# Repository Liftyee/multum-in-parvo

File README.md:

# multum-in-parvo
Low power, high performance mesh radio device

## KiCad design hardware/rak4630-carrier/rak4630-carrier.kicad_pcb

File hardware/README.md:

# Multum in Parvo — KiCad 8 engineering draft

**Revision A is still under development. Do not order or populate this draft.** The native project uses KiCad 8 schematic format 20231120 and PCB format 20240108. Validation runs with installed `kicad-cli 8.0.9`; no KiCad 9/10 format conversion is used. Open `mesh-node.kicad_pro`. All symbols and footprints are project-local.

The schematic has been captured and passes ERC. PCB routing and ground-return review are in progress. The current DRC report records the outstanding connections; a report with zero clearance violations alone does not mean the board is complete. Fabrication release requires zero unconnected items, a deliberate RF/power layout review, and completion of the checks below.

## Architecture

Solar feeds AEM10300; its storage pin joins PACK+. The battery supplies transmit pulses directly. BQ29700 and two common-drain AO3400A N-channel MOSFETs interrupt the negative cell lead. **CELL_N belongs only to the cell connector and protection circuit. Every load, charger return, programmer ground and shield connects to system GND / PACK−.** Raw BAT+ and protected PACK+ are electrically the same positive conductor in this low-side protection topology.

TPS63900 makes always-on 3.3 V. STM32WLE5CCU6 uses its low-power RF output, pin 22, with the ST MB1720 high-band low-power matching circuit. Pin 23, the high-power output, remains unconnected. A BGS12SN6 selects TX/RX for the normal population. The alternate path uses SKY66423-11 with its EK3 868 MHz matching/filter network and pack-referenced controls. MAX17048 is optional. TPS22919 supplies a peripheral connector carrying switched power and GND only.

The system needs an STM32WLE5 firmware/board port; this hardware is not a claim of existing drop-in Meshtastic firmware compatibility.

## Stack and RF geometry

Proposed stack: 2 layers, 0.8 mm finished board, 35 µm copper per side, approximately 0.73 mm dielectric, FR-4 Er 4.5, ENIG, 20 µm soldermask with assumed Er 3.8. RF corridors use top grounded coplanar waveguide, 0.75 mm trace and 0.25 mm side gap, with a continuous bottom reference. The 2-D quasi-static finite-volume calculation gives **50.65 Ω** at 10 µm grid resolution and 50.46 Ω at 20 µm. See `reports/field-impedance.json`; the earlier conformal approximation is retained separately for comparison.

These are proposed material properties, not guaranteed JLCPCB controlled impedance. Confirm the actual offered 0.8 mm stack and measure a coupon. The finite-box calculation does not include pad launches, component parasitics, connector transitions or RF matching. Short narrow launches at fine-pitch parts require VNA tuning. Two layers are quantitatively feasible; a switch to four layers is not justified by the line width.

Ordinary clearance is 0.15 mm, with 0.20 mm ordinary signal routing preferred where space allows. Vias use 0.60/0.30 mm copper/drill. Power routing uses wider conductors and will be reviewed for bottlenecks before release. RF signal routing is restricted to the top layer. Routing output alone is not sufficient: copper pours, stitching and visual ground continuity must also pass review.

## Configuration and operating assumptions

- Solar panel **worst-case cold Voc ≤4.3 V**, providing margin below AEM10300's 4.5 V recommended SRC limit. Its 5.5 V absolute maximum is not an operating target. A nominal 6 V panel is unsuitable.
- AEM10300 straps: STO_CFG=0000 gives 4.05 V charge, 3.50 V ready and 3.00 V low status; R_MPP=100 selects 80% Voc; T_MPP=01 selects nominal 4.5 s/70.8 ms sampling. EN_HP is high; charge is independently inhibited by the temperature/solar-valid logic and MCU.
- Four 100 µF/10 V/1210 storage capacitors are provided. The manufacturer requires at least 100 µF **effective** capacitance with an absent battery. DC-bias/temperature derating of the exact selected capacitor remains a release check.
- TPS63900: CFG3=16.2 kΩ for 3.3 V at SEL=0; CFG1=36.5 kΩ and CFG2=0 also select 3.3 V/unlimited current in the alternate state. Configuration resistors are 1%.
- BQ29700 nominal overcharge/undervoltage levels are 4.275/2.800 V. Normal firmware operating floor is 3.0 V with burst-droop margin. Protection is independent of firmware.
- AO3400A replaces CSD16301Q2 because it specifies ≤48 mΩ at 2.5 V gate drive. Two devices give ≤96 mΩ at 25 °C: 28.8 mV drop and 8.64 mW at 300 mA, excluding traces/connectors. Temperature and protection-threshold tolerances still need inclusion in the final current-path review.
- AQ3118E-01ETG replaces the suggested ESD part: 18 V bidirectional standoff and 0.3 pF typical capacitance accommodate the 7.08 V RF peak at +27 dBm into 50 Ω. A 5 V standoff diode is inappropriate at that power. ESD system performance must be tested.

## RF firmware requirements

BGS12SN6 draws 100 µA typical/180 µA maximum while powered. PA11 supplies its VDD, following the GPIO-supply option in the ST reference. Before sleep set CTRL=0, then PA11=0; keep CTRL low while the switch is unpowered. On wake drive PA11 high and wait at least 20 µs before transmitting. CTRL=0 selects RF1/TX; CTRL=1 selects RF2/RX.

FEM controls have pack-referenced high levels and default low. Allow at least 1 ms for the high-value level-translation networks to settle. Configure the radio's LP PA, start at −9 dBm conducted drive, verify output with an attenuator/load and spectrum analyzer, and never exceed the FEM's +10 dBm TX-input absolute maximum. Firmware must enforce regional output-power, antenna-gain and duty-cycle restrictions. +27 dBm is not universally permitted in EU868.

## Estimated standby budget

No board current has been measured. Typical component figures are not worst-case system guarantees.

| Contributor | Approximate standby contribution | Conditions |
|---|---:|---|
| BQ29700 | 4 µA | Omitted with externally protected pack |
| TPS63900 | 0.075 µA | Typical quiescent figure, conversion losses additional |
| STM32WLE5 | ~1 µA class | Stop 2 + RTC; configuration dependent |
| TPS22919 | 0.002 µA typical | OFF; datasheet permits up to 0.8 µA over full temperature |
| MAX17048 | ~3 µA | Hibernate, optional/DNP; active mode higher |
| BGS12SN6 | Supply driven low in sleep | GPIO/switch leakage must be measured |
| Temperature divider | No direct battery divider load | Powered from solar-valid output only |
| Temperature comparators/supervisor | Solar supplied | ~0.82 µA nominal combined IC current |
| AEM10300 | Unresolved in selected high-power mode | 5.9 nA figure applies to EN_HP=LOW, not the selected HIGH strap |
| FEM and translation | Optional/DNP | Shutdown leakage needs full-temperature audit |

Known default contributions are about 5.1 µA before AEM high-power-mode current, GPIO/MOSFET leakage, capacitor leakage and converter losses. The single-digit ancillary target is plausible but **not yet verified**. A continuously high BGS supply would alone defeat it; the circuit now explicitly avoids that.

## Bring-up sequence after layout release

1. Inspect all bridges, orientation marks, exposed pads and mutually exclusive population options. Leave antenna disconnected and all supplies off.
2. Check resistance between PACK+, GND and CELL_N. Verify protection MOSFET body-diode orientation. Use a current-limited battery simulator before attaching a cell.
3. Verify BQ cutoff/recovery and confirm that solar, debug and peripheral grounds cannot bypass the protector.
4. Sweep the temperature sensor resistance and solar voltage. Confirm EN_STO_CH goes low for absent/shorted NTC, out-of-window temperature, reset MCU and insufficient solar voltage. Measure response delay and leakage.
5. Check 3V3_AON, regulator startup, ripple and droop with pulsed loads. Verify all RF supply nodes before enabling the radio.
6. Attach SWD, test both oscillators, calibrate HSE loading/trim, verify RTC and deep-sleep current with debug detached.
7. Test normal RF with a suitable conducted load/attenuation. Tune matching and filter values with a VNA; measure harmonics, RX sensitivity and switching transients.
8. Fit the FEM variant only after the normal radio works. Verify control truth table/default shutdown and output power starting at minimum drive. Repeat spectral, RX and current-pulse checks.
9. Repeat temperature, battery cutoff/recovery, absent-battery and low-light tests across the intended operating range. Attach the real battery last.

## Release checks still open

Finish routing and ground pours/stitching; inspect both layers; resolve DRC including connectivity and schematic parity; verify every custom footprint against the manufacturer's drawing; verify exact capacitor derating and inductor land patterns; close charge-enable pullup/logic margins and temperature qualification; audit crystal startup/load/frequency tolerance; audit all sleep leakage at temperature; finish silk/test-point labels and connector orientation review. Only then export a fabrication set, assembly positions and final BOM.

See `population-options.md`, `temperature-analysis.md`, `sources/urls.json` and `reports/` for supporting material. Draft BOM entries that contain only an electrical value still require a purchasable manufacturer part number before fabrication release.

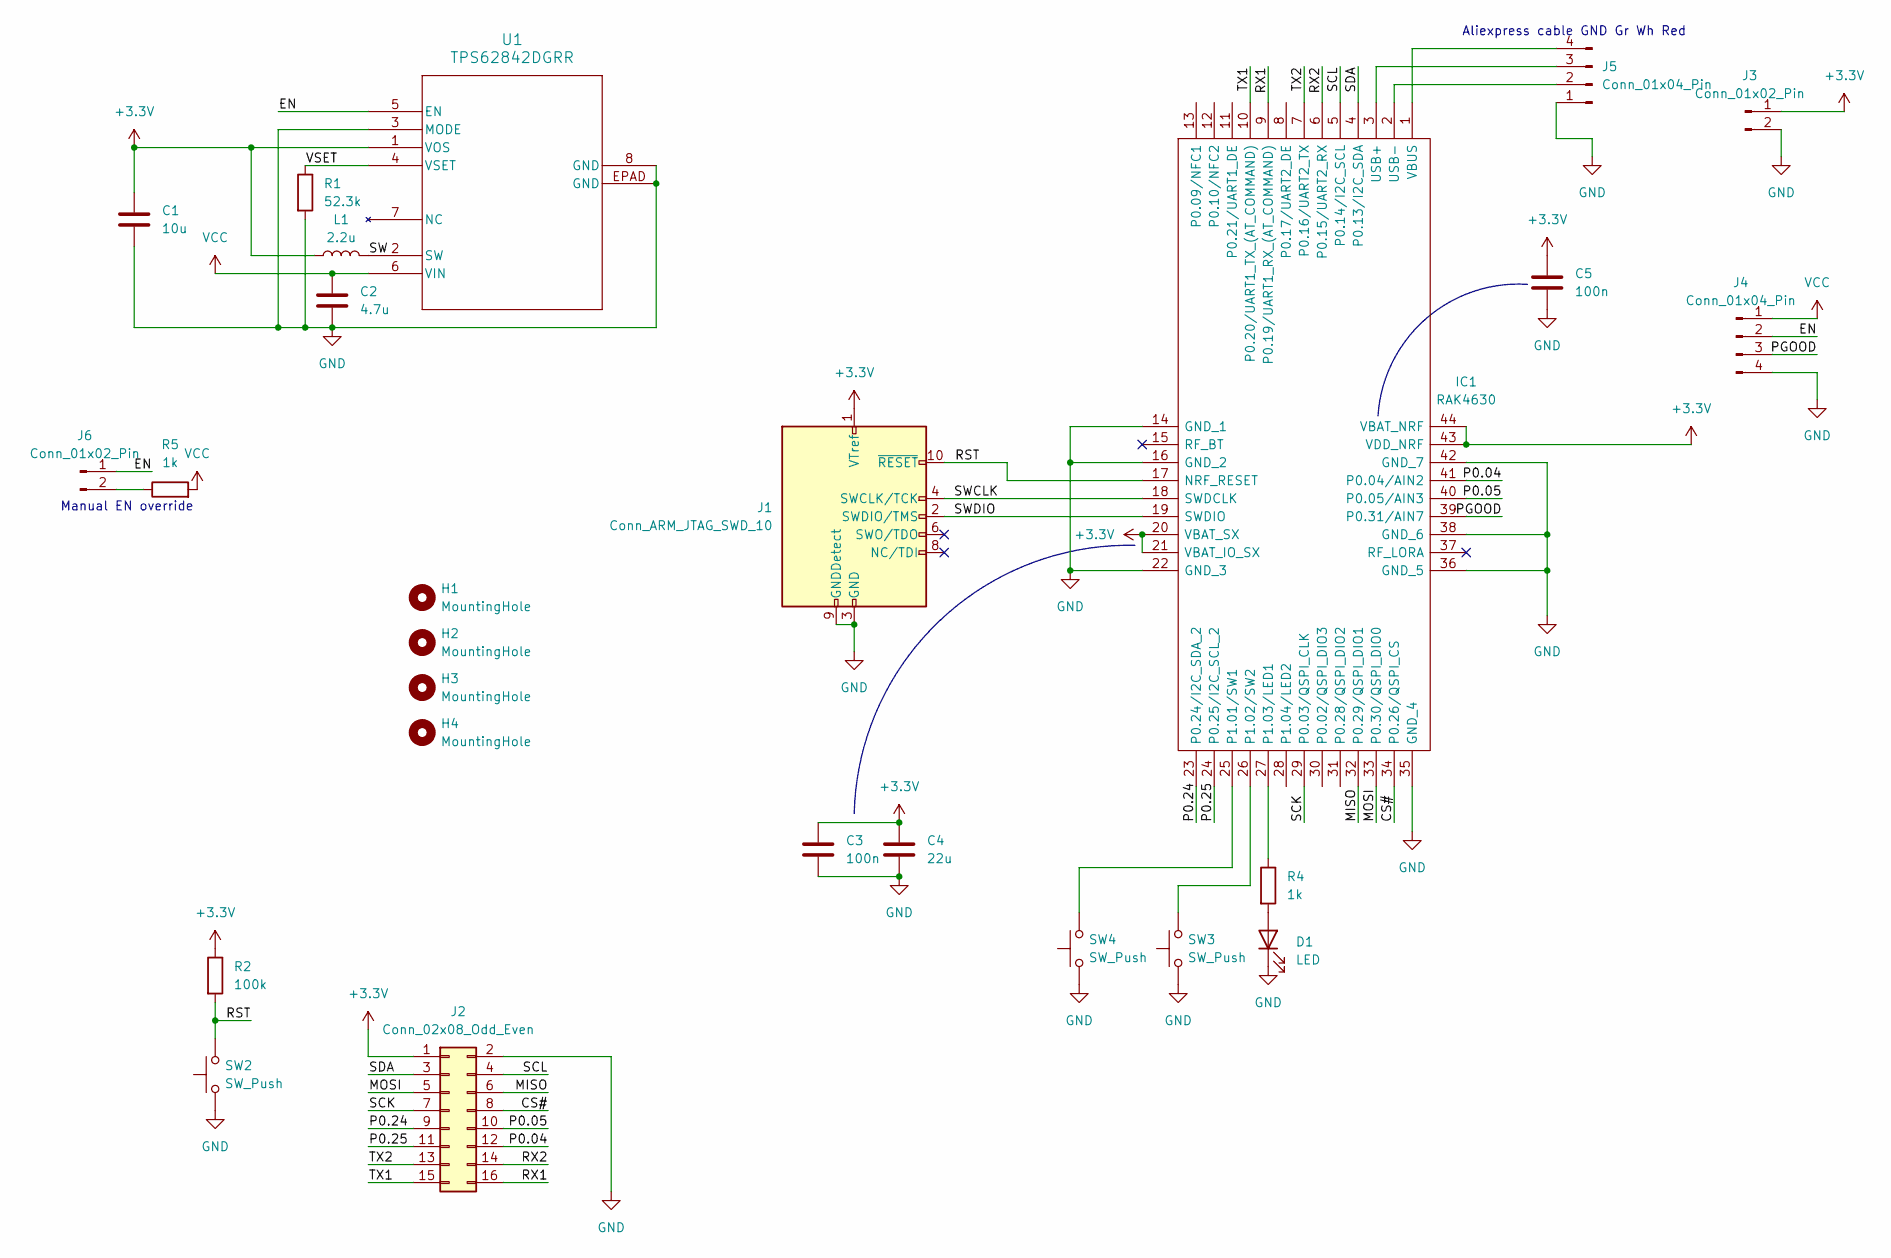
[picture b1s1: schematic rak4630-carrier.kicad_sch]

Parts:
C1: 10u; C_0805_2012Metric
C2: 4.7u; C_0805_2012Metric
C3, C5: 100n; C_0805_2012Metric
C4: 22u; C_0805_2012Metric
D1: LED; LED_0805_2012Metric
H1, H2, H3, H4: MountingHole; MountingHole_3.2mm_M3
IC1: RAK4630; Manufacturer_Part_Number RAK4630
J1: Conn_ARM_JTAG_SWD_10; PinHeader_2x05_P1.27mm_Vertical
J2: Conn_02x08_Odd_Even; PinHeader_2x08_P2.54mm_Vertical
J3: Conn_01x02_Pin; JST_XH_B2B-XH-A_1x02_P2.50mm_Vertical
J4: Conn_01x04_Pin; JST_XH_B4B-XH-A_1x04_P2.50mm_Vertical
J5: Conn_01x04_Pin; JST_PH_B4B-PH-K_1x04_P2.00mm_Vertical
J6: Conn_01x02_Pin; PinHeader_1x02_P2.54mm_Vertical
L1: 2.2u; L_Murata_DFE201610P
R1: 52.3k; R_0805_2012Metric
R2: 100k; R_0805_2012Metric
R4, R5: 1k; R_0805_2012Metric
SW2, SW3, SW4: SW_Push; Aliexpress_TLZWLA_SMD_Button_4mm
U1: TPS62842DGRR; HVSSOP8_DGR_TEX

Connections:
+3.3V: C1.1, C3.1, C4.1, C5.1, IC1.20 (VBAT_SX), IC1.21 (VBAT_IO_SX), IC1.43 (VDD_NRF), IC1.44 (VBAT_NRF), J1.1 (VTref), J2.1, J3.1, L1.1, R2.1, U1.1 (VOS)
/CS#: IC1.34 (P0.26/QSPI_CS), J2.8
/EN: J4.2, J6.1, U1.5 (EN)
/MISO: IC1.32 (P0.29/QSPI_DIO1), J2.6
/MOSI: IC1.33 (P0.30/QSPI_DIO0), J2.5
/P0.04: IC1.41 (P0.04/AIN2), J2.12
/P0.05: IC1.40 (P0.05/AIN3), J2.10
/P0.24: IC1.23 (P0.24/I2C_SDA_2), J2.9
/P0.25: IC1.24 (P0.25/I2C_SCL_2), J2.11
/PGOOD: IC1.39 (P0.31/AIN7), J4.3
/RST: IC1.17 (NRF_RESET), J1.10 (~RESET), R2.2, SW2.2
/RX1: IC1.9 (P0.19/UART1_RX_(AT_COMMAND)), J2.16
/RX2: IC1.6 (P0.15/UART2_RX), J2.14
/SCK: IC1.29 (P0.03/QSPI_CLK), J2.7
/SCL: IC1.5 (P0.14/I2C_SCL), J2.4
/SDA: IC1.4 (P0.13/I2C_SDA), J2.3
/SW: L1.2, U1.2 (SW)
/SWCLK: IC1.18 (SWDCLK), J1.4 (SWCLK/TCK)
/SWDIO: IC1.19 (SWDIO), J1.2 (SWDIO/TMS)
/TX1: IC1.10 (P0.20/UART1_TX_(AT_COMMAND)), J2.15
/TX2: IC1.7 (P0.16/UART2_TX), J2.13
/VSET: R1.1, U1.4 (VSET)
GND: C1.2, C2.2, C3.2, C4.2, C5.2, D1.1 (K), IC1.14 (GND_1), IC1.16 (GND_2), IC1.22 (GND_3), IC1.35 (GND_4), IC1.36 (GND_5), IC1.38 (GND_6), IC1.42 (GND_7), J1.3 (GND), J1.5 (GND), J1.9 (GNDDetect), J2.2, J3.2, J4.4, J5.1, R1.2, SW2.1, SW3.1, SW4.1, U1.3 (MODE), U1.8 (GND), U1.EPAD (GND)
unnamed: D1.2 (A), R4.2
unnamed: IC1.25 (P1.01/SW1), SW4.2
unnamed: IC1.26 (P1.02/SW2), SW3.2
unnamed: IC1.27 (P1.03/LED1), R4.1
unnamed: IC1.3 (USB+), J5.3
unnamed: IC1.2 (USB-), J5.2
unnamed: IC1.1 (VBUS), J5.4
unnamed: J6.2, R5.1
VCC: C2.1, J4.1, R5.2, U1.6 (VIN)

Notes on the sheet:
Manual EN override
Aliexpress cable GND Gr Wh Red

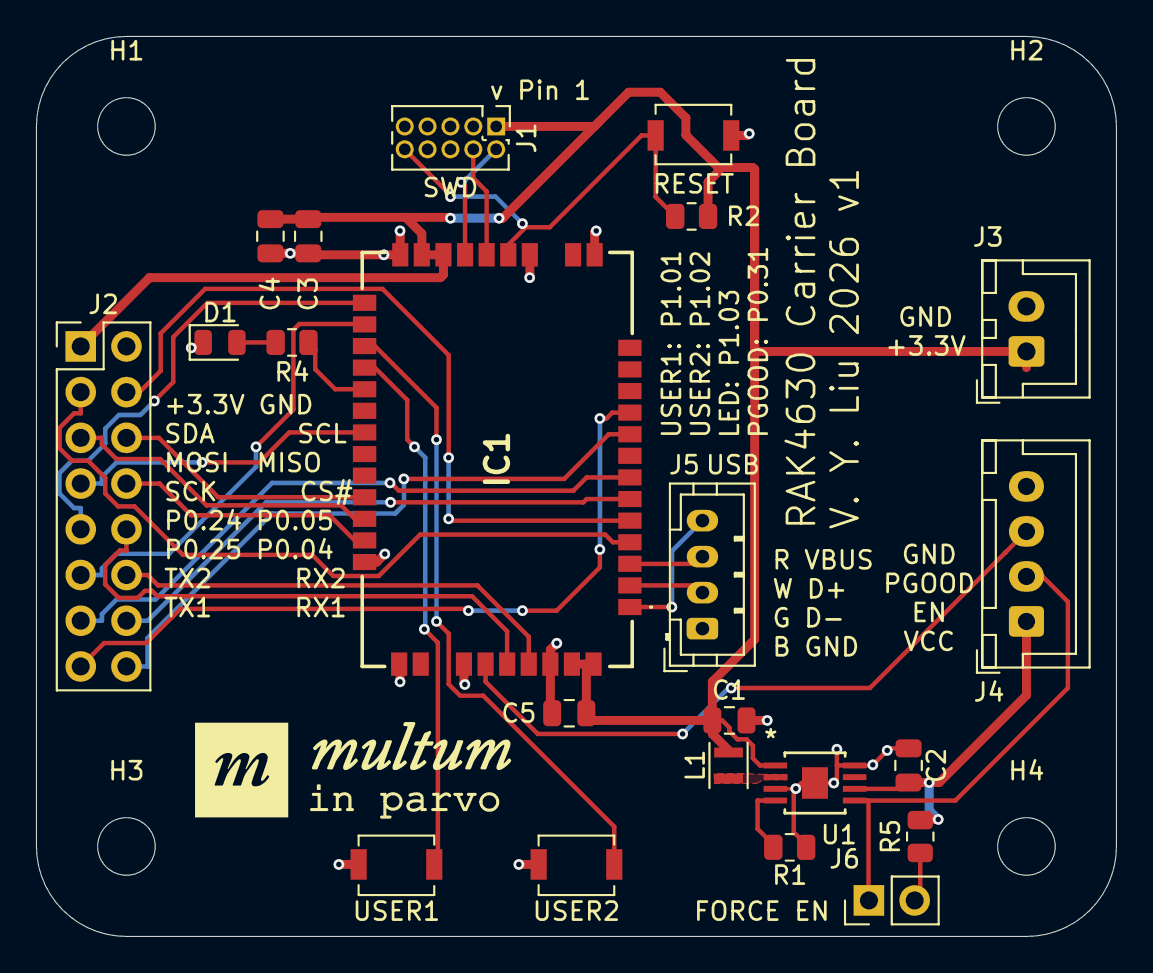
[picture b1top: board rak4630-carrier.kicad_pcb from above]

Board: 2 copper layers, 60.0 x 50.0 mm, 26 parts (0 on the bottom side), 32 nets.

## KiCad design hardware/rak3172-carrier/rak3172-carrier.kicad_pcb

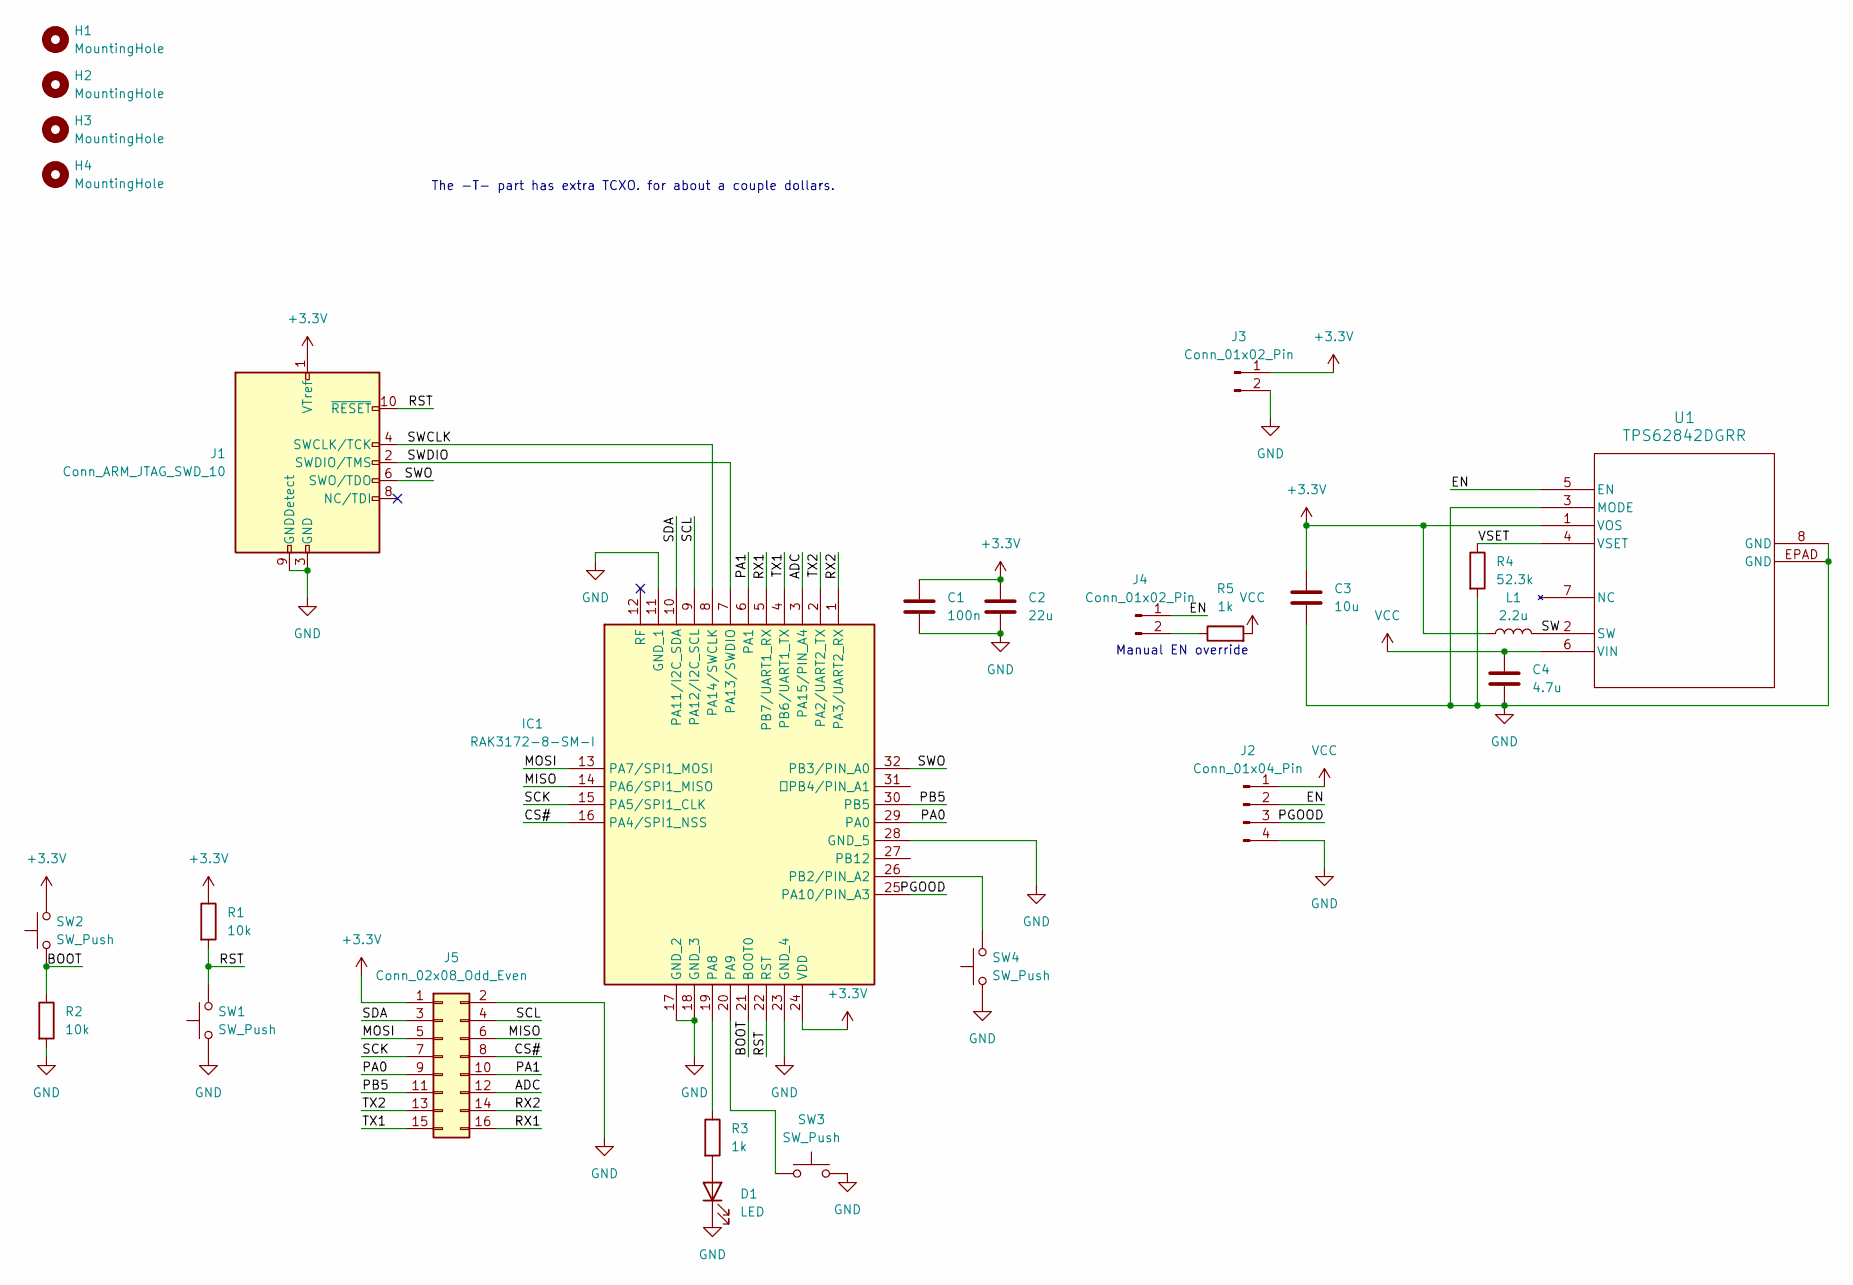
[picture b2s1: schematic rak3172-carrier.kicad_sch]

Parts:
C1: 100n; C_0805_2012Metric
C2: 22u; C_0805_2012Metric
C3: 10u; C_0805_2012Metric
C4: 4.7u; C_0805_2012Metric
D1: LED; LED_0805_2012Metric
H1, H2, H3, H4: MountingHole; MountingHole_3.2mm_M3
IC1: RAK3172-8-SM-I; RAK31729SMNI; Manufacturer_Part_Number RAK3172-9-SM-NI
J1: Conn_ARM_JTAG_SWD_10; PinHeader_2x05_P1.27mm_Vertical
J2: Conn_01x04_Pin; JST_XH_B4B-XH-A_1x04_P2.50mm_Vertical
J3: Conn_01x02_Pin; JST_XH_B2B-XH-A_1x02_P2.50mm_Vertical
J4: Conn_01x02_Pin; PinHeader_1x02_P2.54mm_Vertical
J5: Conn_02x08_Odd_Even; PinHeader_2x08_P2.54mm_Vertical
L1: 2.2u; L_Murata_DFE201610P
R1, R2: 10k; R_0805_2012Metric
R3, R5: 1k; R_0805_2012Metric
R4: 52.3k; R_0805_2012Metric
SW1, SW2, SW3, SW4: SW_Push; Aliexpress_TLZWLA_SMD_Button_4mm
U1: TPS62842DGRR; HVSSOP8_DGR_TEX

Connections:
+3.3V: C1.1, C2.1, C3.1, IC1.24 (VDD), J1.1 (VTref), J3.1, J5.1, L1.1, R1.1, SW2.2, U1.1 (VOS)
/ADC: IC1.3 (PA15/PIN_A4), J5.12
/BOOT: IC1.21 (BOOT0), R2.1, SW2.1
/CS#: IC1.16 (PA4/SPI1_NSS), J5.8
/EN: J2.2, J4.1, U1.5 (EN)
/MISO: IC1.14 (PA6/SPI1_MISO), J5.6
/MOSI: IC1.13 (PA7/SPI1_MOSI), J5.5
/PA0: IC1.29 (PA0), J5.9
/PA1: IC1.6 (PA1), J5.10
/PB5: IC1.30 (PB5), J5.11
/PGOOD: IC1.25 (PA10/PIN_A3), J2.3
/RST: IC1.22 (RST), J1.10 (~RESET), R1.2, SW1.2
/RX1: IC1.5 (PB7/UART1_RX), J5.16
/RX2: IC1.1 (PA3/UART2_RX), J5.14
/SCK: IC1.15 (PA5/SPI1_CLK), J5.7
/SCL: IC1.9 (PA12/I2C_SCL), J5.4
/SDA: IC1.10 (PA11/I2C_SDA), J5.3
/SW: L1.2, U1.2 (SW)
/SWCLK: IC1.8 (PA14/SWCLK), J1.4 (SWCLK/TCK)
/SWDIO: IC1.7 (PA13/SWDIO), J1.2 (SWDIO/TMS)
/SWO: IC1.32 (PB3/PIN_A0), J1.6 (SWO/TDO)
/TX1: IC1.4 (PB6/UART1_TX), J5.15
/TX2: IC1.2 (PA2/UART2_TX), J5.13
/VSET: R4.1, U1.4 (VSET)
GND: C1.2, C2.2, C3.2, C4.2, D1.1 (K), IC1.11 (GND_1), IC1.17 (GND_2), IC1.18 (GND_3), IC1.23 (GND_4), IC1.28 (GND_5), J1.3 (GND), J1.5 (GND), J1.9 (GNDDetect), J2.4, J3.2, J5.2, R2.2, R4.2, SW1.1, SW3.2, SW4.1, U1.3 (MODE), U1.8 (GND), U1.EPAD (GND)
unnamed: D1.2 (A), R3.2
unnamed: IC1.19 (PA8), R3.1
unnamed: IC1.20 (PA9), SW3.1
unnamed: IC1.26 (PB2/PIN_A2), SW4.2
unnamed: J4.2, R5.1
VCC: C4.1, J2.1, R5.2, U1.6 (VIN)

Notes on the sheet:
The -T- part has extra TCXO. for about a couple dollars.
Manual EN override

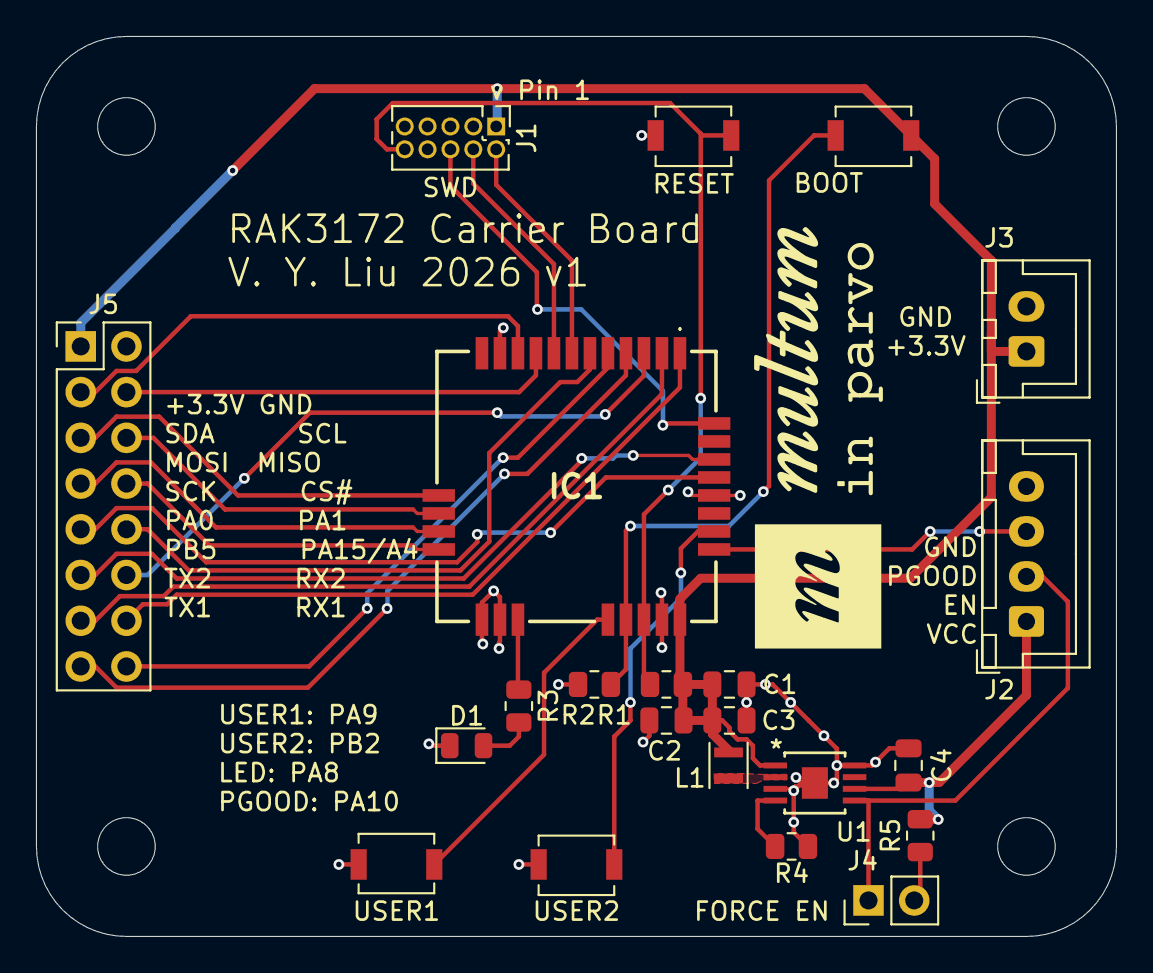
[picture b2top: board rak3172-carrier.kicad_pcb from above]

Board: 2 copper layers, 60.0 x 50.0 mm, 26 parts (0 on the bottom side), 31 nets.

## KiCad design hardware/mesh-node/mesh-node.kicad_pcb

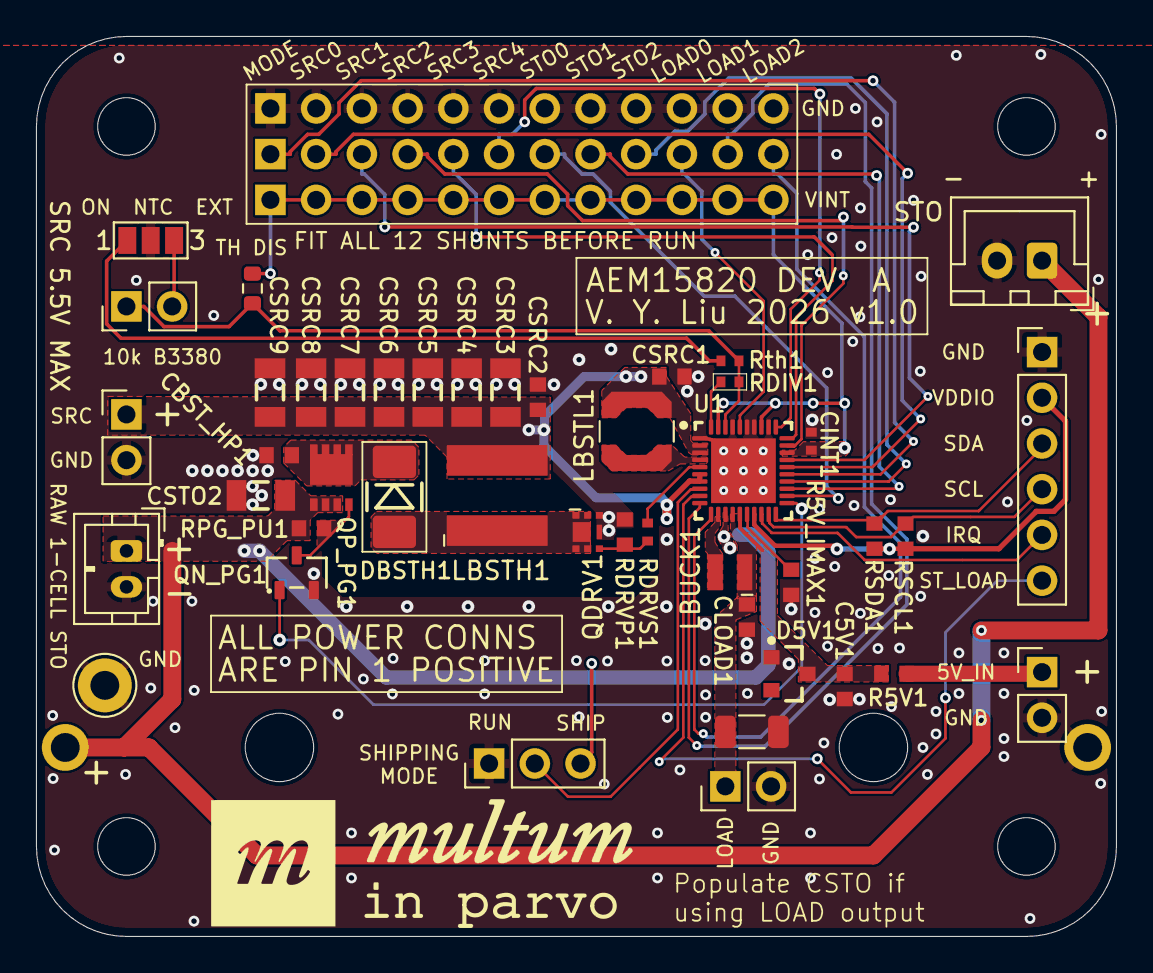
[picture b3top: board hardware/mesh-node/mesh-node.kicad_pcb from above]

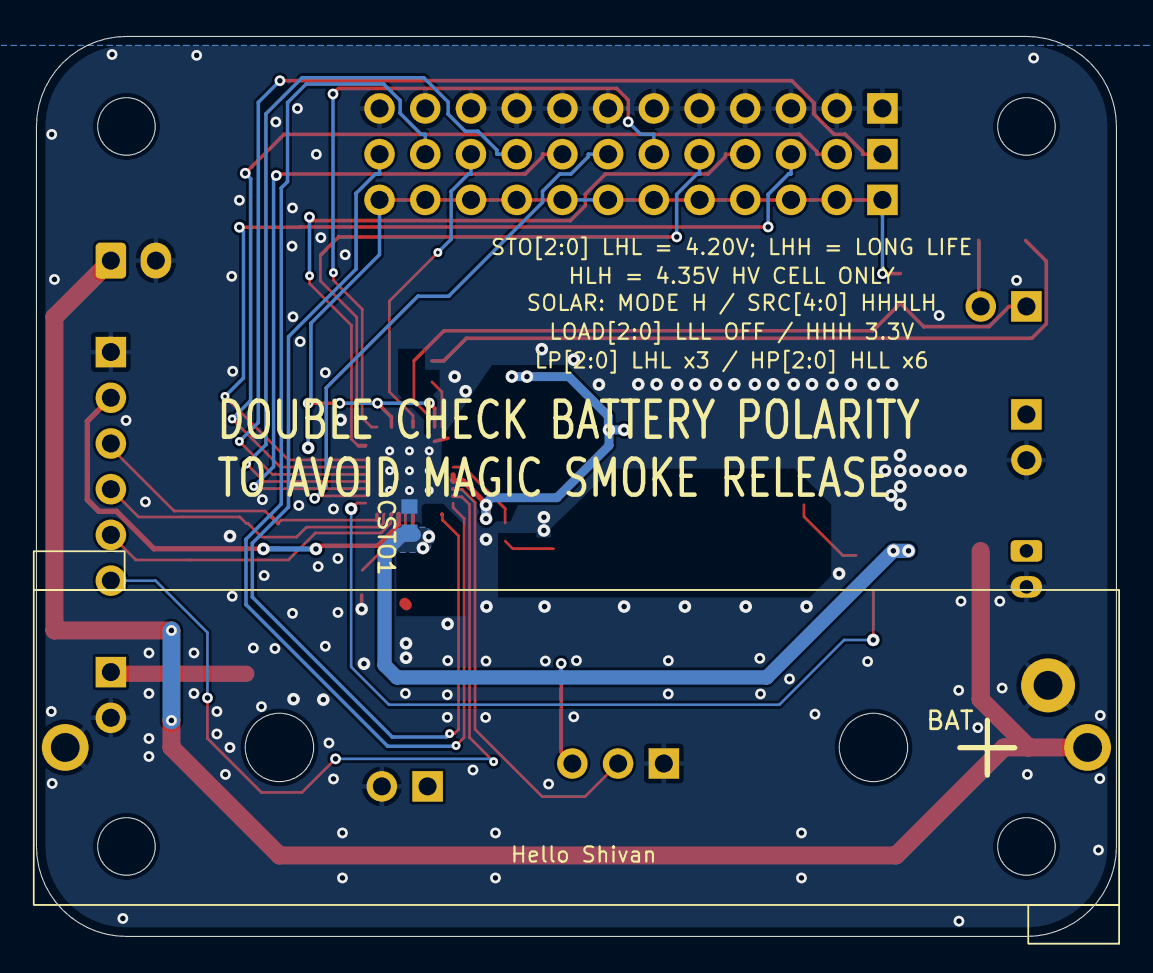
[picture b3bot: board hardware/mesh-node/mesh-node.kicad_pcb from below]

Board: 2 copper layers, 60.0 x 50.0 mm, 53 parts (2 on the bottom side), 38 nets.

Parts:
BAT: Bulgin BX0035 Battery Holder
C5V1: 47uF; AEM_Donor_C0603_[1608]
CBST_HP1: 47uF; AEM_Donor_C0603_[1608]
CINT1: 10uF; AEM_Donor_C0402_[1005]
CLOAD1: 22uF; AEM_Donor_C0603_[1608]
CLOAD2: OPTIONAL 220uF; C_1206_3216Metric
CSRC1, CSRC2: 22uF; AEM_Donor_C0603_[1608]
CSRC3, CSRC4, CSRC5, CSRC6, CSRC7, CSRC8, CSRC9: 220uF; AEM_Donor_C1206_[3216]
CSTO1: 47uF; AEM_Donor_C0603_[1608]
CSTO2: 220uF; AEM_Donor_C1206_[3216]
D5V1: 5.1V; AEM_Donor_SOT23-3P__3x1.40mm_Pitch=0.915mm_diode_AK
DBSTH1: VS-10BQ015; AEM_Donor_DO-214AA
H1, H2, H3, H4: M3; MountingHole_3.2mm_M3
J5V1: J5V1; PinHeader_1x02_P2.54mm_Vertical
JCFG1: LOW / GND; PinHeader_1x12_P2.54mm_Vertical
JCFG2: SIGNALS; PinHeader_1x12_P2.54mm_Vertical
JCFG3: HIGH / VINT; PinHeader_1x12_P2.54mm_Vertical
JIO1: JIO1; PinHeader_1x06_P2.54mm_Vertical
JLOAD1: JLOAD1; PinHeader_1x02_P2.54mm_Vertical
JNTC1: EXT NTC 10k B3380; PinHeader_1x02_P2.54mm_Vertical
JPNTC1: ONBOARD / EXTERNAL; SolderJumper-3_P1.3mm_Open_Pad1.0x1.5mm_NumberLabels
JSHIP1: RUN / SHIP; PinHeader_1x03_P2.54mm_Vertical
JSRC1: JSRC1; PinHeader_1x02_P2.54mm_Vertical
JSTO1: STO+ / STO-; JST_PH_2
LBSTH1: 3.3uH; L_Wurth_74438367033
LBSTL1: 33uH; L_Coilcraft_LPS4018
LBUCK1: 10uH; L_TDK_VLS252012CX
QDRV1: RF4E100AJ; ROHM_HUML2020L8_RF4E100AJ
QN_PG1: BSS138N; AEM_Donor_SOT23-3L_STM-L
QP_PG1: DMP2005UFG; DMP2005UFG_PowerDI3333_8_GSD
R5V1: 2.2R 0.1W; AEM_Donor_Resistor_0603_[1608]
R5V_IMAX1: 1.5k / 33.3mA; AEM_Donor_Resistor_0603_[1608]
RDIV1: 22k; AEM_Donor_Resistor_0402
RDRVP1: 330k; AEM_Donor_Resistor_0603_[1608]
RDRVS1: 0R; AEM_Donor_Resistor_0402
RPG_PU1: 330k; AEM_Donor_Resistor_0603_[1608]
RSCL1: 1k; AEM_Donor_Resistor_0603_[1608]
RSDA1: 1k; AEM_Donor_Resistor_0603_[1608]
RTHDIS1: 0R / THERMAL DISABLE; R_0603_1608Metric
Rth1: 10k B3380; AEM_Donor_Resistor_0402
STO: JST_XH_B2B-XH-A_1x02_P2.50mm_Vertical
TPSTO2: TP_STO-; TestPoint_THTPad_D3.0mm_Drill1.5mm
U1: AEM15820; AEM15820_QFN40

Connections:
5V_IMAX: R5V_IMAX1.2, U1.16
5V_IN: C5V1.2, D5V1.1, R5V1.2, U1.15
5V_IN_EXT: J5V1.1, R5V1.1
BST_HP_DRV: RDRVS1.2, U1.5
BST_HP_PG: QN_PG1.1, U1.21
GND: BAT.2, C5V1.1, CBST_HP1.1, CINT1.1, CLOAD1.1, CLOAD2.2, CSRC1.1, CSRC2.1, CSRC3.1, CSRC4.1, CSRC5.1, CSRC6.1, CSRC7.1, CSRC8.1, CSRC9.1, CSTO1.1, CSTO2.1, D5V1.2, J5V1.2, JCFG1.1, JCFG1.2, JCFG1.3, JCFG1.4, JCFG1.5, JCFG1.6, JCFG1.7, JCFG1.8, JCFG1.9, JCFG1.10, JCFG1.11, JCFG1.12, JIO1.1, JLOAD1.2, JPNTC1.2, JSHIP1.1, JSRC1.2, JSTO1.2, QDRV1.4, QDRV1.8, QN_PG1.2, R5V_IMAX1.1, RDRVP1.1, STO.2, TPSTO2.1, U1.1, U1.32, U1.34, U1.35, U1.37, U1.41
IRQ: JIO1.5, U1.18
LOAD: CLOAD1.2, CLOAD2.1, JLOAD1.1, LBUCK1.1, U1.14
LOAD_CFG_0: JCFG2.10, U1.36
LOAD_CFG_1: JCFG2.11, U1.10
LOAD_CFG_2: JCFG2.12, U1.11
NTC_EXT_RETURN: JNTC1.2, JPNTC1.3
NTC_ON_RETURN: JPNTC1.1, Rth1.1
NetCBST_HP_2: CBST_HP1.2, DBSTH1.1, QP_PG1.3
NetDBSTH_A: DBSTH1.2, LBSTH1.1, QDRV1.1, QDRV1.2, QDRV1.5, QDRV1.6, QDRV1.7
NetQDRV_1: QDRV1.3, RDRVP1.2, RDRVS1.1
NetQN_PG_3: QN_PG1.3, QP_PG1.1, RPG_PU1.1
NetRdiv_1: JNTC1.1, RDIV1.1, RTHDIS1.1, Rth1.2, U1.38
NetRdiv_2: RDIV1.2, U1.40
SCL: JIO1.4, RSCL1.1, U1.19
SDA: JIO1.3, RSDA1.1, U1.20
SHIP_MODE: JSHIP1.2, U1.8
SRC: CSRC1.2, CSRC2.2, CSRC3.2, CSRC4.2, CSRC5.2, CSRC6.2, CSRC7.2, CSRC8.2, CSRC9.2, JSRC1.1, LBSTH1.2, LBSTL1.2, U1.2, U1.3, U1.6, U1.7
SRC_CFG_0: JCFG2.2, U1.26
SRC_CFG_1: JCFG2.3, U1.27
SRC_CFG_2: JCFG2.4, U1.29
SRC_CFG_3: JCFG2.5, U1.30
SRC_CFG_4: JCFG2.6, U1.31
SRC_MODE: JCFG2.1, U1.25
STO: BAT.1, CSTO1.2, CSTO2.2, JSHIP1.3, JSTO1.1, QP_PG1.2, RPG_PU1.2, STO.1, U1.13
STO_CFG_0: JCFG2.7, U1.22
STO_CFG_1: JCFG2.8, U1.23
STO_CFG_2: JCFG2.9, U1.24
ST_LOAD: JIO1.6, U1.9
SWBST_LP: LBSTL1.1, U1.4
SWBUCK: LBUCK1.2, U1.12
VDDIO: JIO1.2, RSCL1.2, RSDA1.2, U1.17
VINT: CINT1.2, JCFG3.1, JCFG3.2, JCFG3.3, JCFG3.4, JCFG3.5, JCFG3.6, JCFG3.7, JCFG3.8, JCFG3.9, JCFG3.10, JCFG3.11, JCFG3.12, RTHDIS1.2, U1.28, U1.33, U1.39
